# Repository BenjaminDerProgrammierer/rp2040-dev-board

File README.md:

# RP2040 Dev Board

My take on the RP2040 Dev Board (See [guide](https://blueprint.hackclub.com/starter-projects/devboard))

## Why?

I wanted to progress my ESP32 Dev Board, but I had little experience with PCBs. So, I decided to start with the RP2040, which seemed easier, following the guide.

## A few images

## Bill of Materials (BOM)

| Qty | Description |
| ---: | --- |
| 1 | USB‑C receptacle (USB2.0) |
| 2 | 27 Ω 0402 resistor |
| 4 | 1 µF 0402 capacitor |
| 10 | 0.1 µF 0402 capacitor |
| 1 | 3‑pin 2.54 mm vertical pin header |
| 2 | 5.1 kΩ 0402 resistor |
| 2 | 1 kΩ 0402 resistor |
| 1 | MCP1700 3.3V LDO regulator (SOT‑23) |
| 1 | W25Q16 16Mbit SPI flash (USON‑8) |
| 1 | 10 kΩ 0402 resistor |
| 2 | 20‑pin 2.54 mm vertical pin headers |
| 1 | RP2040 microcontroller (QFN‑56) |
| 2 | 33 pF 0402 capacitor |
| 1 | 12 MHz SMD crystal (3225) |
| 1 | Push button (SPST, momentary) |

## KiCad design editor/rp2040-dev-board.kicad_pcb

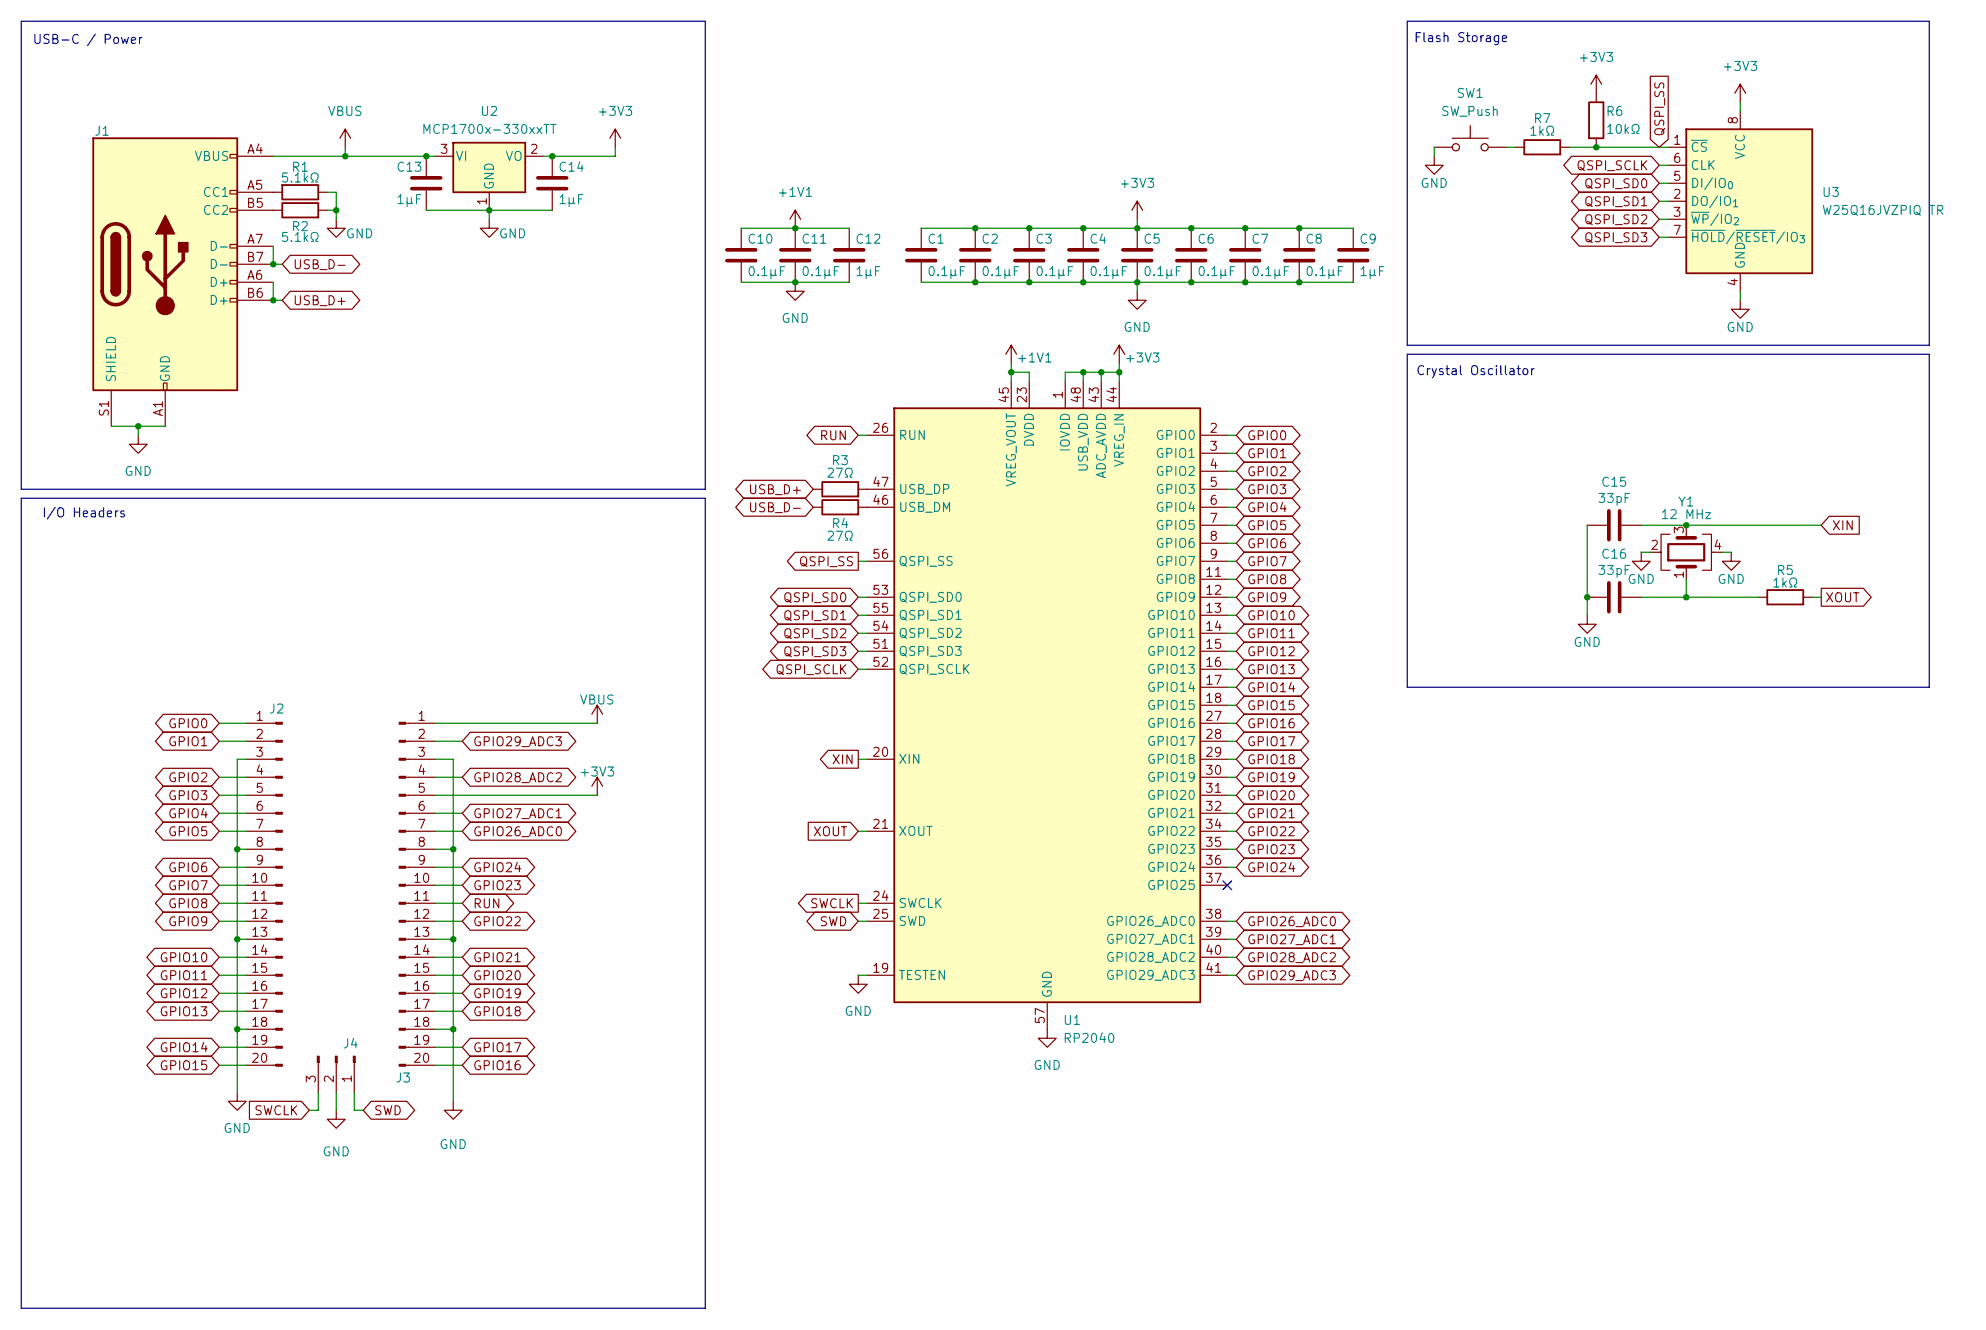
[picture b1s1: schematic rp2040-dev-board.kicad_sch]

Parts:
C1, C2, C3, C4, C5, C6, C7, C8, C10, C11: 0.1µF; C_0402_1005Metric
C9, C12, C13, C14: 1µF; C_0402_1005Metric
C15, C16: 33pF; C_0402_1005Metric
J1: USB_C_Receptacle_USB2.0_14P; USB_C_Receptacle_HRO_TYPE-C-31-M-12
J2, J3: Conn_01x20_Pin; PinSocket_1x20_P2.54mm_Vertical
J4: Conn_01x03_Pin; PinSocket_1x03_P2.54mm_Vertical
R1, R2: 5.1kΩ; R_0402_1005Metric
R3, R4: 27Ω; R_0402_1005Metric
R5, R7: 1kΩ; R_0402_1005Metric
R6: 10kΩ; R_0402_1005Metric
SW1: SW_Push; SW_Push_SPST_NO_Alps_SKRK
U1: RP2040; QFN-56-1EP_7x7mm_P0.4mm_EP3.2x3.2mm
U2: MCP1700x-330xxTT; SOT-23
U3: W25Q16JVZPIQ TR; Winbond_USON-8-1EP_3x2mm_P0.5mm_EP0.2x1.6mm
Y1: 12 MHz; Crystal_SMD_3225-4Pin_3.2x2.5mm

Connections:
+1V1: C10.1, C11.1, C12.1, U1.23 (DVDD), U1.45 (VREG_VOUT), U1.50 (DVDD)
+3V3: C1.1, C2.1, C3.1, C4.1, C5.1, C6.1, C7.1, C8.1, C9.1, C14.1, J3.5, R6.1, U1.1 (IOVDD), U1.10 (IOVDD), U1.22 (IOVDD), U1.33 (IOVDD), U1.42 (IOVDD), U1.43 (ADC_AVDD), U1.44 (VREG_IN), U1.48 (USB_VDD), U1.49 (IOVDD), U2.2 (VO), U3.8 (VCC)
GND: C1.2, C2.2, C3.2, C4.2, C5.2, C6.2, C7.2, C8.2, C9.2, C10.2, C11.2, C12.2, C13.2, C14.2, C15.1, C16.1, J1.A1 (GND), J1.A12 (GND), J1.B1 (GND), J1.B12 (GND), J1.S1 (SHIELD), J2.3, J2.8, J2.13, J2.18, J3.3, J3.8, J3.13, J3.18, J4.2, R1.1, R2.2, SW1.1, U1.19 (TESTEN), U1.57 (GND), U2.1 (GND), U3.4 (GND), Y1.2, Y1.4
GPIO0: J2.1, U1.2 (GPIO0)
GPIO1: J2.2, U1.3 (GPIO1)
GPIO2: J2.4, U1.4 (GPIO2)
GPIO3: J2.5, U1.5 (GPIO3)
GPIO4: J2.6, U1.6 (GPIO4)
GPIO5: J2.7, U1.7 (GPIO5)
GPIO6: J2.9, U1.8 (GPIO6)
GPIO7: J2.10, U1.9 (GPIO7)
GPIO8: J2.11, U1.11 (GPIO8)
GPIO9: J2.12, U1.12 (GPIO9)
GPIO10: J2.14, U1.13 (GPIO10)
GPIO11: J2.15, U1.14 (GPIO11)
GPIO12: J2.16, U1.15 (GPIO12)
GPIO13: J2.17, U1.16 (GPIO13)
GPIO14: J2.19, U1.17 (GPIO14)
GPIO15: J2.20, U1.18 (GPIO15)
GPIO16: J3.20, U1.27 (GPIO16)
GPIO17: J3.19, U1.28 (GPIO17)
GPIO18: J3.17, U1.29 (GPIO18)
GPIO19: J3.16, U1.30 (GPIO19)
GPIO20: J3.15, U1.31 (GPIO20)
GPIO21: J3.14, U1.32 (GPIO21)
GPIO22: J3.12, U1.34 (GPIO22)
GPIO23: J3.10, U1.35 (GPIO23)
GPIO24: J3.9, U1.36 (GPIO24)
GPIO26_ADC0: J3.7, U1.38 (GPIO26_ADC0)
GPIO27_ADC1: J3.6, U1.39 (GPIO27_ADC1)
GPIO28_ADC2: J3.4, U1.40 (GPIO28_ADC2)
GPIO29_ADC3: J3.2, U1.41 (GPIO29_ADC3)
unnamed: C16.2, R5.1, Y1.1
unnamed: J1.A5 (CC1), R1.2
unnamed: J1.B5 (CC2), R2.1
unnamed: R7.1, SW1.2
unnamed: R4.2, U1.46 (USB_DM)
unnamed: R3.2, U1.47 (USB_DP)
QSPI_SCLK: U1.52 (QSPI_SCLK), U3.6 (CLK)
QSPI_SD0: U1.53 (QSPI_SD0), U3.5 (DI/IO_{0})
QSPI_SD1: U1.55 (QSPI_SD1), U3.2 (DO/IO_{1})
QSPI_SD2: U1.54 (QSPI_SD2), U3.3 (~WP/IO_{2})
QSPI_SD3: U1.51 (QSPI_SD3), U3.7 (~HOLD/~RESET/IO_{3})
QSPI_SS: R6.2, R7.2, U1.56 (QSPI_SS), U3.1 (~CS)
RUN: J3.11, U1.26 (RUN)
SWCLK: J4.3, U1.24 (SWCLK)
SWD: J4.1, U1.25 (SWD)
USB_D+: J1.A6 (D+), J1.B6 (D+), R3.1
USB_D-: J1.A7 (D-), J1.B7 (D-), R4.1
VBUS: C13.1, J1.A4 (VBUS), J1.A9 (VBUS), J1.B4 (VBUS), J1.B9 (VBUS), J3.1, U2.3 (VI)
XIN: C15.2, U1.20 (XIN), Y1.3
XOUT: R5.2, U1.21 (XOUT)

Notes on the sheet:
Flash Storage
USB-C / Power
Crystal Oscillator
I/O Headers

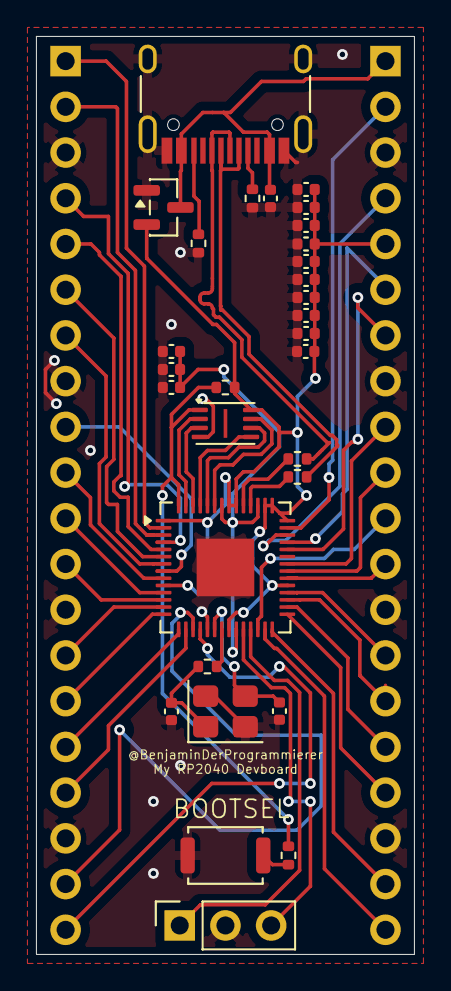
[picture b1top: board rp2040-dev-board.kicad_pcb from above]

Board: 2 copper layers, 21.0 x 51.0 mm, 32 parts (0 on the bottom side), 52 nets.

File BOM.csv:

Id,Designator,Footprint,Quantity,Comment,Supplier and ref
1,J1,USB_C_Receptacle_HRO_TYPE-C-31-M-12,1,USB_C_Receptacle_USB2.0_14P,
2,"R4,R3",R_0402_1005Metric,2,27Ω,
3,"C14,C13,C9,C12",C_0402_1005Metric,4,1µF,
4,"C1,C5,C4,C2,C6,C7,C8,C3,C10,C11",C_0402_1005Metric,10,0.1µF,
5,J4,PinSocket_1x03_P2.54mm_Vertical,1,Conn_01x03_Pin,
6,"R1,R2",R_0402_1005Metric,2,5.1kΩ,
7,"R7,R5",R_0402_1005Metric,2,1kΩ,
8,U2,SOT-23,1,MCP1700x-330xxTT,
9,U3,Winbond_USON-8-1EP_3x2mm_P0.5mm_EP0.2x1.6mm,1,W25Q16JVZPIQ TR,
10,R6,R_0402_1005Metric,1,10kΩ,
11,"J2,J3",PinSocket_1x20_P2.54mm_Vertical,2,Conn_01x20_Pin,
12,U1,QFN-56-1EP_7x7mm_P0.4mm_EP3.2x3.2mm,1,RP2040,
13,"C16,C15",C_0402_1005Metric,2,33pF,
14,Y1,Crystal_SMD_3225-4Pin_3.2x2.5mm,1,12 MHz,
15,SW1,SW_Push_SPST_NO_Alps_SKRK,1,SW_Push,

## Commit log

2025-11-29 Update structure
